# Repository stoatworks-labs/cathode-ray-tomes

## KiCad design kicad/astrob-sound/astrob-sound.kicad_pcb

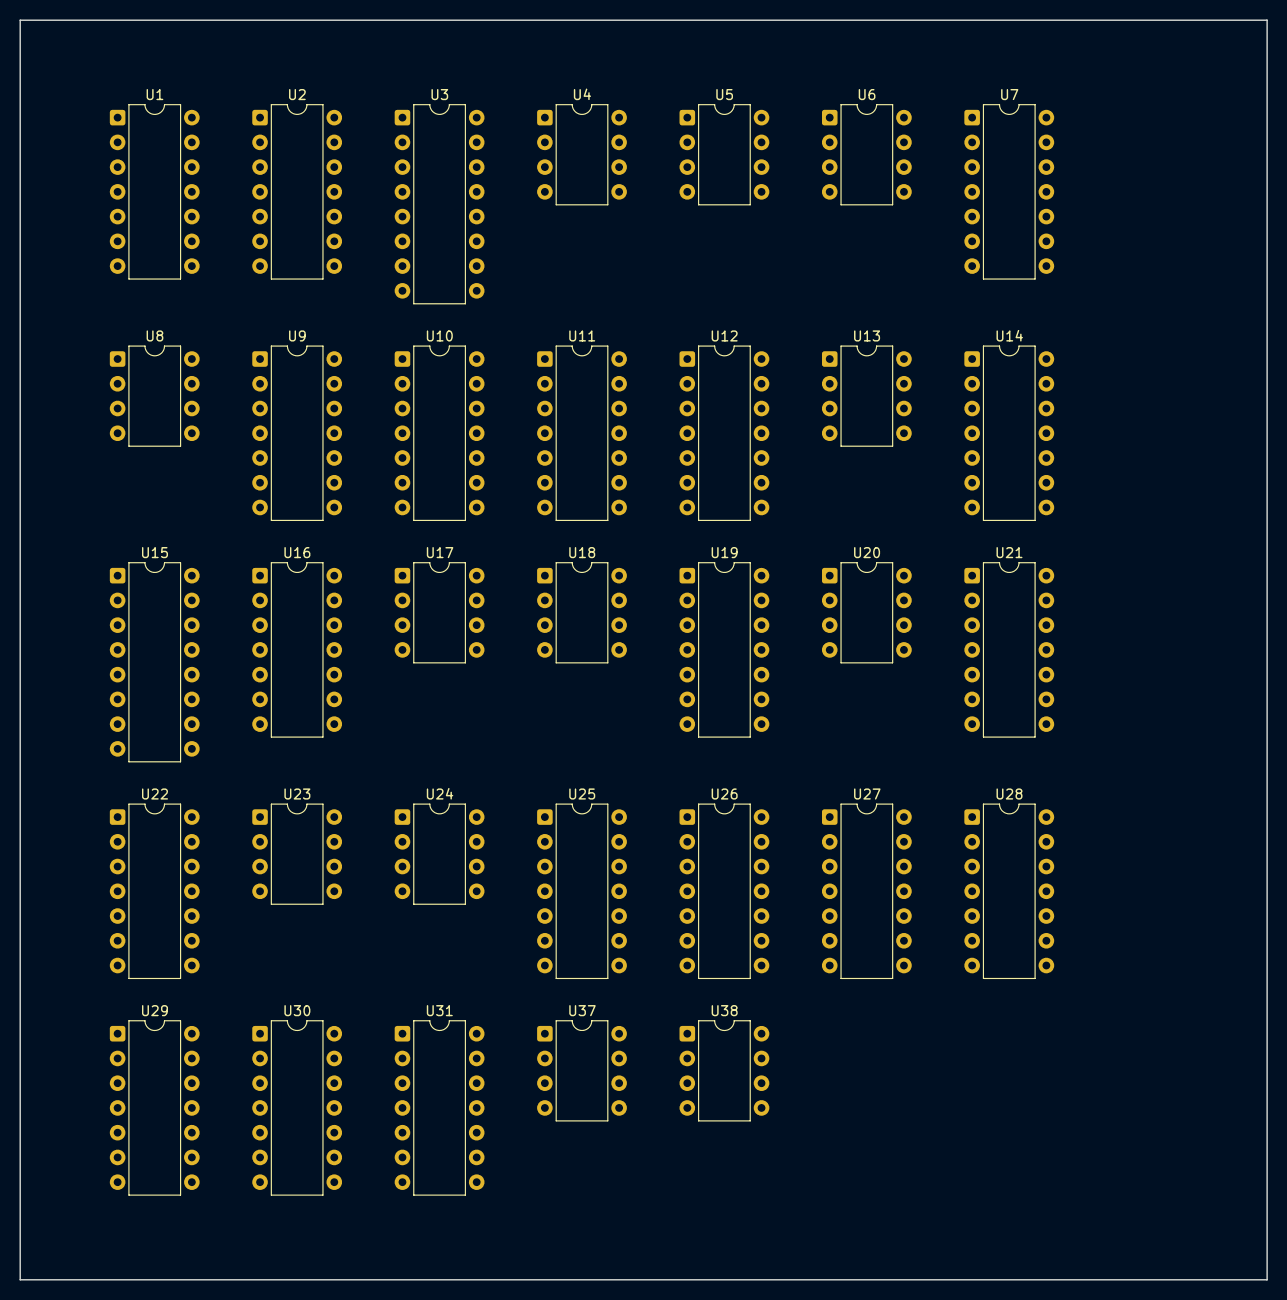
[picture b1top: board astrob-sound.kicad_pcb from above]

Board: 2 copper layers, 128.0 x 129.3 mm, 33 parts (0 on the bottom side), 61 nets, no tracks yet.

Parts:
U1, U2, U7, U16, U22: TL084; DIP-14_W7.62mm
U3, U15: CD4017; DIP-16_W7.62mm
U4, U5, U6, U13, U17, U18, U20, U23, U24, U37, U38: NE555; DIP-8_W7.62mm
U8: MM5837; DIP-8_W7.62mm
U9, U10, U11, U21, U25, U27: CD4011; DIP-14_W7.62mm
U12, U14, U19, U28: CD4024; DIP-14_W7.62mm
U26, U29: 7407; DIP-14_W7.62mm
U30, U31: 7406; DIP-14_W7.62mm

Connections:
+5V: U26.14, U29.14, U30.14, U31.14
+12V: U1.4, U2.4, U3.16, U4.8, U5.8, U6.4, U6.8, U7.4, U8.4, U9.14, U10.14, U11.14, U12.14, U13.8, U14.14, U15.16, U16.4, U17.8, U18.8, U19.14, U20.8, U21.14, U22.4, U23.8, U24.8, U25.14, U27.14, U28.14, U37.4, U37.8, U38.8
-12V: U1.11, U2.11, U7.11, U8.2, U16.11, U22.11
GND: U1.3, U1.5, U1.10, U1.12, U2.3, U2.5, U2.10, U2.12, U3.8, U3.13, U4.1, U5.1, U6.1, U7.12, U8.1, U9.7, U10.7, U11.7, U12.7, U13.1, U14.7, U15.8, U15.13, U17.1, U18.1, U19.7, U20.1, U21.7, U22.3, U22.5, U22.10, U22.12, U23.1, U24.1, U25.7, U26.7, U27.7, U28.7, U29.7, U30.7, U31.7, U37.1, U38.1
I_ATTACK_RATE: U21.5, U26.2
I_BONUS: U10.6, U29.8
I_INVADER_1: U18.4, U23.4, U31.2
I_INVADER_2: U13.4, U31.4
I_INVADER_3: U17.4, U31.10
I_INVADER_4: U31.8, U38.4
I_LASER_1: U25.9, U26.6
I_LASER_2: U25.12, U26.4
I_LONG_EXPL: U26.8, U27.6
I_RATE_RESET: U15.15, U31.12
I_REFILL: U3.15, U29.10
I_SHORT_EXPL: U26.10, U27.2
I_SONAR: U11.1, U29.6
LO_D6: U29.11, U30.3
unnamed: U9.5, U9.6
unnamed: U3.14, U9.3
unnamed: U11.12, U11.13
unnamed: U11.10, U12.2
unnamed: U17.2, U17.6
unnamed: U4.2, U4.6
unnamed: U5.4, U9.11
unnamed: U9.8, U9.9
unnamed: U38.2, U38.6
unnamed: U5.2, U5.6
unnamed: U6.2, U6.6
unnamed: U10.8, U10.9
unnamed: U13.2, U13.6
unnamed: U18.6, U18.7
unnamed: U23.2, U23.6
unnamed: U37.2, U37.6
unnamed: U16.1, U16.2
unnamed: U14.2, U25.3
unnamed: U19.2, U25.4
unnamed: U24.2, U24.6
unnamed: U20.2, U20.6
unnamed: U7.8, U7.9
unnamed: U21.12, U21.13
unnamed: U21.8, U21.9
unnamed: U24.4, U25.5, U25.6, U25.10
unnamed: U20.4, U25.1, U25.2, U25.11
unnamed: U27.4, U27.8, U27.9
unnamed: U4.5, U5.5
unnamed: U9.1, U9.2, U9.4
unnamed: U11.8, U11.9, U11.11
unnamed: U4.4, U9.10, U9.12, U9.13
unnamed: U10.10, U10.12, U10.13
unnamed: U27.3, U27.12, U27.13
unnamed: U10.1, U10.2, U10.4
unnamed: U11.3, U11.5, U11.6
unnamed: U12.1, U13.3
unnamed: U14.1, U20.3
unnamed: U15.14, U21.1, U21.2, U21.4
unnamed: U18.2, U23.3
unnamed: U19.1, U24.3
unnamed: U28.1, U37.3
unnamed: U28.2, U28.5
W: U30.5, U30.9, U31.5

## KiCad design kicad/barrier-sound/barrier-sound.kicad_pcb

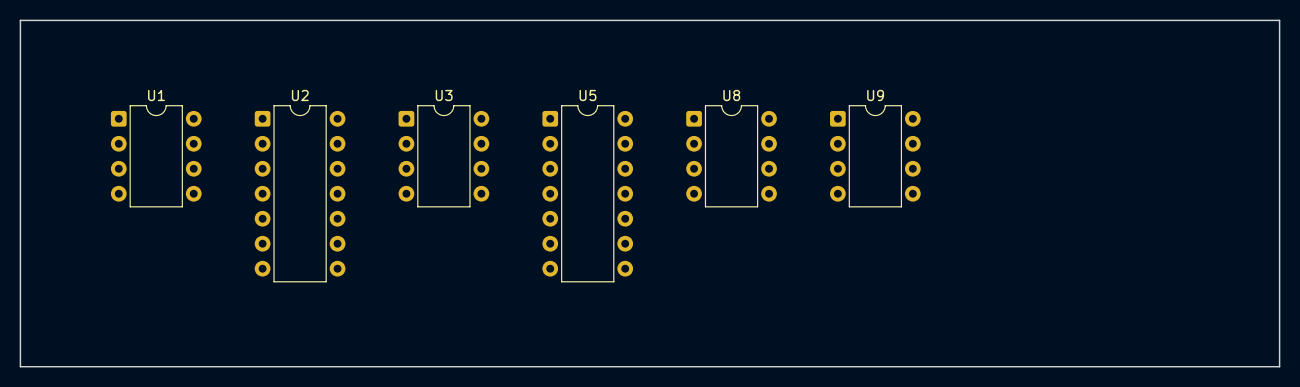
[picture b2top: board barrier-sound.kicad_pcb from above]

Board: 2 copper layers, 128.0 x 35.2 mm, 6 parts (0 on the bottom side), 4 nets, no tracks yet.

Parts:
U1, U3, U8, U9: TL081; DIP-8_W7.62mm
U2: 7406; DIP-14_W7.62mm
U5: TL182; DIP-14_W7.62mm

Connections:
+5V: U2.14, U5.7
+15V: U1.7, U3.7, U5.6, U8.7, U9.7
-15V: U1.4, U3.4, U5.9, U8.4, U9.4
GND: U2.7, U3.3, U5.8, U8.3, U9.3
